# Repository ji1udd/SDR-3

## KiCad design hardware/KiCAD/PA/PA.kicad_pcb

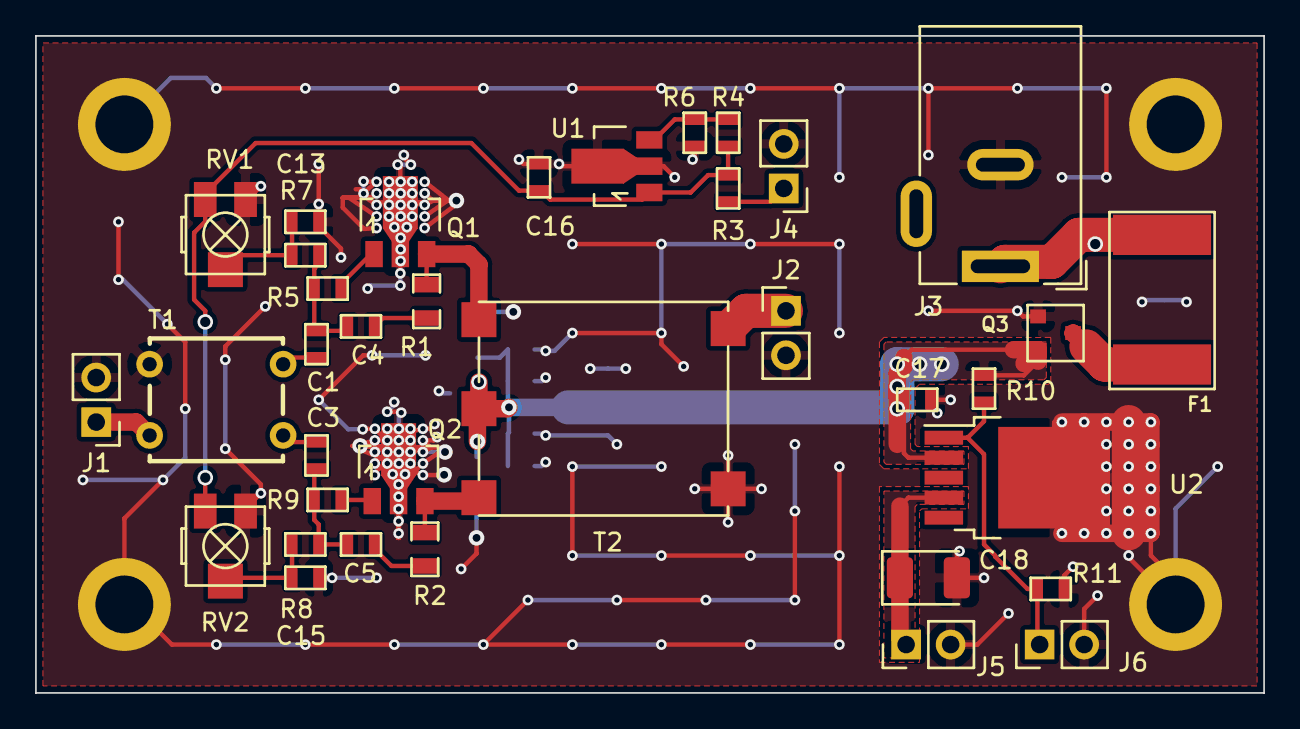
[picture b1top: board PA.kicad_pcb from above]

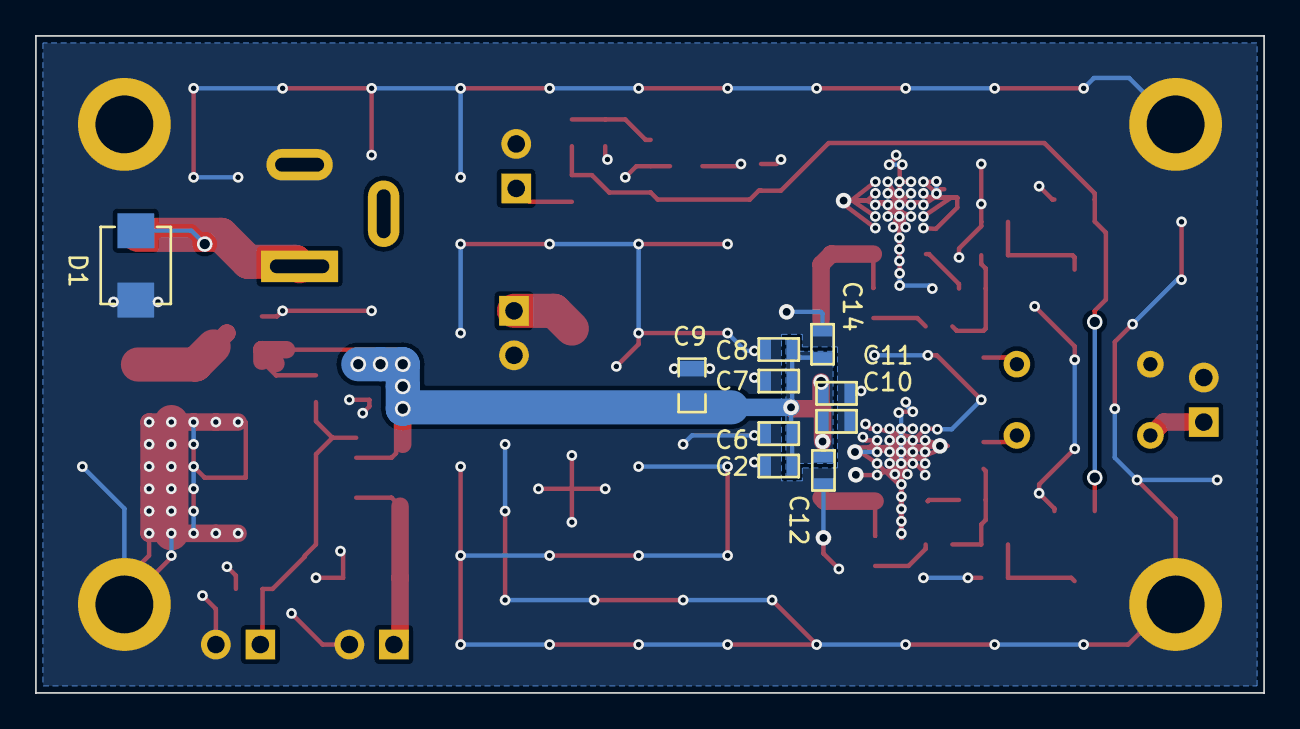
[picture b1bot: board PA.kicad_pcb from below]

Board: 2 copper layers, 70.1 x 37.5 mm, 50 parts (10 on the bottom side), 23 nets.

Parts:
C1, C3, C10, C11, C12, C13, C14, C15: 100n; SM0603
C2, C6, C7, C8, C16: 1u; SM0603
C4, C5: DNI; SM0603
C9: 47u; SM0805
C17: 0.33u; SM0603
C18: 22u; CP_EIA-3528-15_AVX-H_Pad1.50x2.35mm_HandSolder
D1: SMBJ18CA; smbj18ca
F1: Polyfuse; FUSE
J1, J2, J4, J5, J6: Conn_01x02; PinHeader_1x02_P2.54mm_Vertical
J3: Barrel_Jack; BarrelJack_Wuerth_6941xx301002
MH1, MH2, MH3, MH4: TestPoint; m3
Q1, Q2: RFM04U6P; SOT89-3_Housing_RevA_02Sep2012
Q3: DMP3099L; SOT23_3
R1, R2: DNI; SM0805
R3: 2700; SM0603
R4: 470; SM0603
R5, R9: 4.7; SM0603
R6: 1500; SM0603
R7, R8: 100; SM0603
R10: 10k; SM0603
R11: DNI; SM0603
RV1, RV2: 1000; TS4YJ
T1: BN43-2402; BN43-2402_TRNS
T2: B62152A4X30; B62152A4X30_TRNS
U1: TA76431F; SOT89-3_Housing_RevA_02Sep2012
U2: BA50BC0WFP; TO-252-5_TabPin6

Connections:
/7.2V: C2.2, C6.2, C7.2, C8.2, C9.1, C10.2, C11.2, C12.2, C14.2, C17.2, Q3.2, R10.2, T2.2, U2.2
/VG1: C13.1, R7.1, RV1.2
/VG2: C15.1, R8.1, RV2.2
GND: C2.1, C6.1, C7.1, C8.1, C9.2, C10.1, C11.1, C12.1, C13.2, C14.1, C15.2, C16.2, C17.1, C18.2, D1.2, J1.2, J2.2, J3.2, J4.2, J5.2, J6.2, MH1.1, MH2.1, MH3.1, MH4.1, Q1.2, Q2.2, Q3.1, R6.1, R11.1, RV1.3, RV2.3, T1.2, T2.5, U1.2, U2.6
unnamed: C1.1, T1.4
unnamed: C1.2, C4.1, R5.1, R7.2
unnamed: C3.1, T1.3
unnamed: C3.2, C5.1, R8.2, R9.1
unnamed: C4.2, R1.1
unnamed: C5.2, R2.1
unnamed: C16.1, R3.2, R4.2, RV1.1, RV2.1, U1.1
unnamed: C18.1, J5.1, U2.4
unnamed: D1.1, F1.2, J3.1
unnamed: F1.1, Q3.3
unnamed: J1.1, T1.1
unnamed: J2.1, T2.4
unnamed: J4.1, R3.1
unnamed: J6.1, R10.1, R11.2, U2.1
unnamed: Q1.1, R5.2
unnamed: Q1.3, R1.2, T2.1
unnamed: Q2.1, R9.2
unnamed: Q2.3, R2.2, T2.3
unnamed: R4.1, R6.2, U1.3

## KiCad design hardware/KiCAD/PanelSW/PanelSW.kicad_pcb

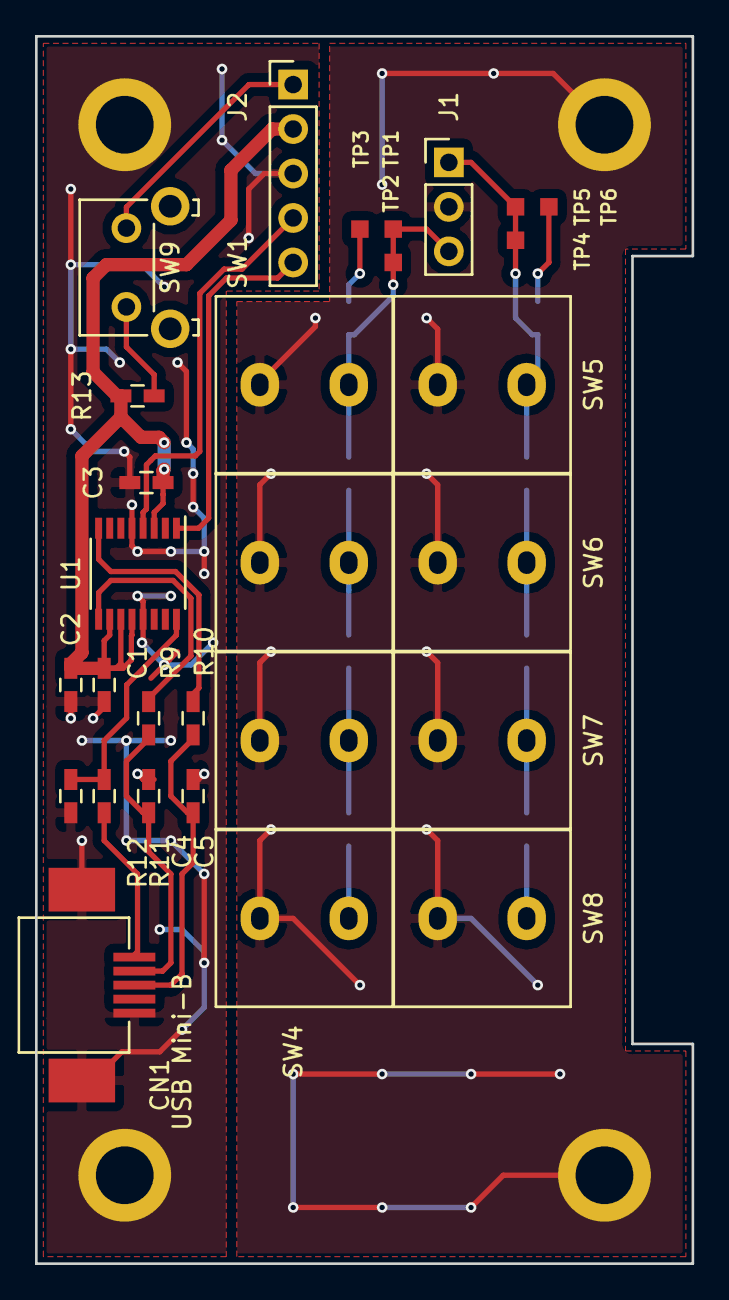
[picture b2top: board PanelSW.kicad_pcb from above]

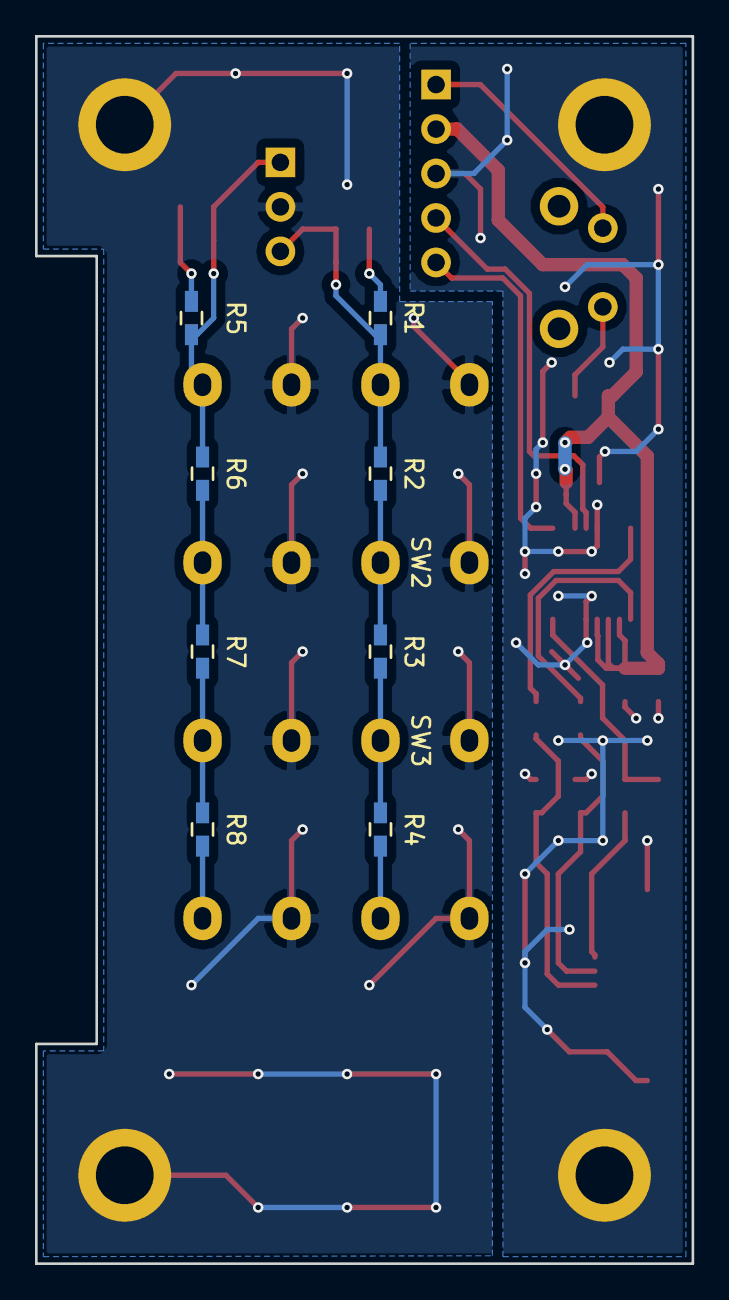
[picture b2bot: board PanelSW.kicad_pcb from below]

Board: 2 copper layers, 37.5 x 70.1 mm, 41 parts (8 on the bottom side), 23 nets.

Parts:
C1, C3: 100n; C_0603_HandSoldering
C2: 4.7u; C_0603_HandSoldering
C4, C5: 47p; C_0603_HandSoldering
CN1: USB Mini-B; UX60SC-MB-5ST
J1: Conn_01x03; PinHeader_1x03_P2.54mm_Vertical
J2: Conn_01x05; PinHeader_1x05_P2.54mm_Vertical
MH1, MH2, MH3, MH4: TestPoint; m3
R1, R5: 220; C_0603_HandSoldering
R2, R6: 270; C_0603_HandSoldering
R3, R7: 330; C_0603_HandSoldering
R4, R8: 470; C_0603_HandSoldering
R9, R10: 27; C_0603_HandSoldering
R11: 4.7k; C_0603_HandSoldering
R12: 10k; C_0603_HandSoldering
R13: 1k; C_0603_HandSoldering
SW1, SW2, SW3, SW4, SW5, SW6, SW7, SW8: SW_Push; SW_CW_DS660RS
SW9: SW_Push; SW_Tactile_SKHH_Angled
TP1, TP2, TP3, TP4, TP5, TP6: TestPoint; TP
U1: FT230XS; SSOP-16_3.9x4.9mm_P0.635mm

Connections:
GND: C1.2, C2.2, C3.2, C4.1, C5.2, CN1.5, CN1.6, CN1.7, J2.3, MH1.1, MH4.1, R12.1, U1.5, U1.13
GNDA: J1.2, MH2.1, MH3.1, SW1.1, SW2.1, SW3.1, SW4.1, SW5.1, SW6.1, SW7.1, SW8.1
unnamed: C1.1, C2.1, C3.1, J2.2, R13.1, U1.3, U1.10, U1.11, U1.12
unnamed: C4.2, CN1.2, R9.2
unnamed: C5.1, CN1.3, R10.2
unnamed: CN1.1, R11.2
unnamed: J1.1, R5.1, R6.2, SW5.2, TP4.1, TP5.1
unnamed: J1.3, R1.1, R2.2, SW1.2, TP1.1, TP2.1
unnamed: J2.1, SW9.2
unnamed: J2.4, U1.4
unnamed: J2.5, U1.1
unnamed: R1.2, TP3.1
unnamed: R2.1, R3.2, SW2.2
unnamed: R3.1, R4.2, SW3.2
unnamed: R4.1, SW4.2
unnamed: R5.2, TP6.1
unnamed: R6.1, R7.2, SW6.2
unnamed: R7.1, R8.2, SW7.2
unnamed: R8.1, SW8.2
unnamed: R9.1, U1.9
unnamed: R10.1, U1.8
unnamed: R11.1, R12.2, U1.16
unnamed: R13.2, SW9.1

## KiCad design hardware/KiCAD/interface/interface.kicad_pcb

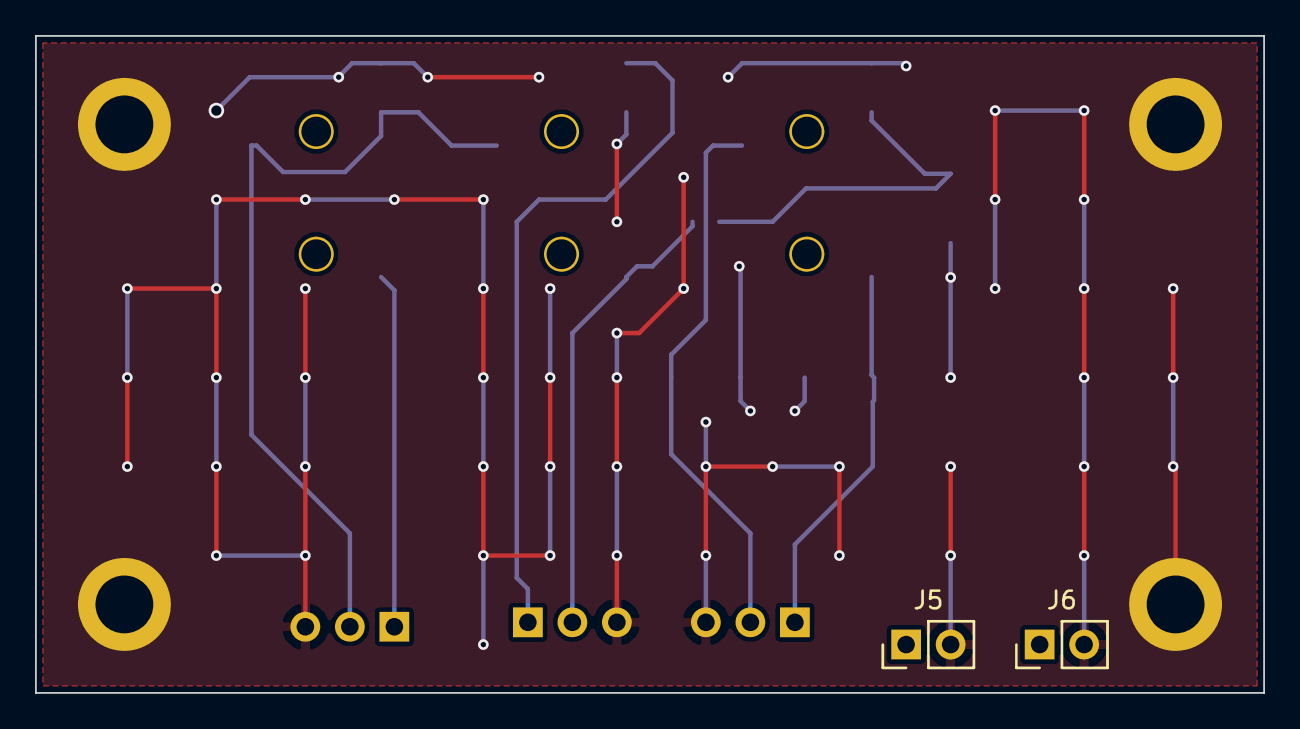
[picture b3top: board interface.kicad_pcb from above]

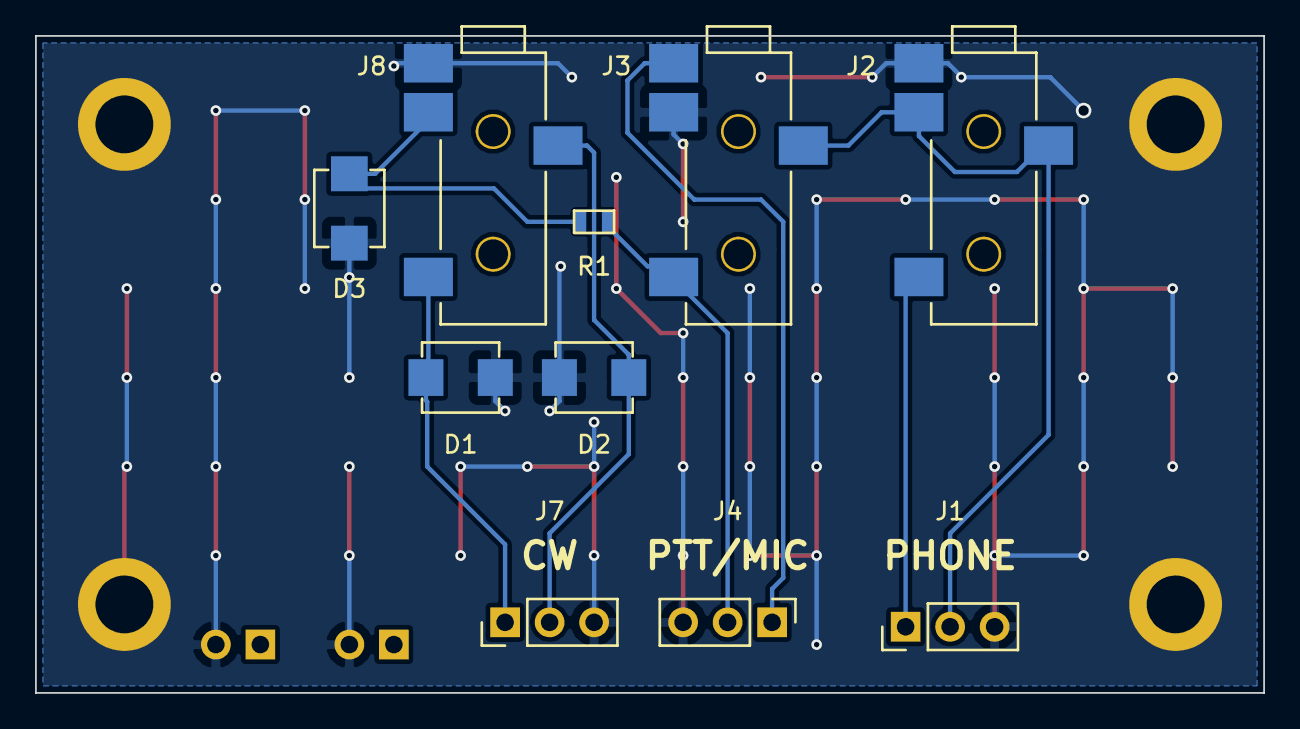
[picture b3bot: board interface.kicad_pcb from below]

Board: 2 copper layers, 70.1 x 37.5 mm, 16 parts (10 on the bottom side), 8 nets.

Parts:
D1, D2, D3: SMBJ18CA; smbj18ca
J1, J4, J7: Conn_01x03; PinHeader_1x03_P2.54mm_Vertical
J2, J3, J8: SJ-43514-SMT
J5, J6: Conn_01x02; PinHeader_1x02_P2.54mm_Vertical
MH1, MH2, MH3, MH4: TestPoint; m3
R1: DNI; SM0603

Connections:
GND: D1.2, D2.2, D3.2, J1.3, J2.1, J3.4, J4.3, J5.2, J6.2, J7.3, J8.1, MH1.1, MH2.1, MH3.1, MH4.1
unnamed: D1.1, J7.1, J8.2
unnamed: D2.1, J7.2, J8.3
unnamed: D3.1, J8.4, R1.1
unnamed: J1.1, J2.2
unnamed: J1.2, J2.3, J2.4, J3.3
unnamed: J3.1, J4.1
unnamed: J3.2, J4.2, R1.2

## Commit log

2018-10-06 1st Summary (Step1 to 4)
2018-10-08 Added Step5 modification
2018-10-12 Added keyer setting menu
2018-10-14 added bug key / straight key function as Step7
2018-10-14 bug fix
2018-10-14 added keyer speed setting on tranceiver as Step8
2018-10-20 added Step9 and Step10
2018-10-22 added 4 type Rx LPF ( fc = 600,700,800,900Hz )
2018-10-24 added CW Rx filter (8th order IIR HPF/LPF) as Step11
2018-10-28 changed CW rise time as Step12
2018-11-13 T2 Mixer LTSpice model
2018-11-16 added T2 Mixer comparison spice model
2018-11-18 Added an analog type S-meter as Step13
2018-11-18 fixed README.md
2018-11-18 Fixed README.md again
2018-11-21 Updated Step13_gui_c_2.txt
2018-11-21 Updated Step13_gui_c_2.jpg (bug fix)
2018-11-25 Update S-meter as Step14. a bitmap data of S-meter panel can be used.
2018-12-01 added Yado-san's designed s-meter and setting as Step15
2018-12-01 added No.2 tips on README.md
2018-12-08 added Makino-san's and Gyofun-san's designed s-meters as Step16
2018-12-19 fixed bugs in Step13 as Step17
2018-12-22 added Tx Meter function as Step18
2018-12-22 fixed type1 and type3 meter on tx
2018-12-27 add Battery voltage monitor (Yado-san's idea) as Step19
2019-01-13 Added Rig communication function as Step20
2019-01-13 no message
2019-01-19 Waterfall is added as Step21
2019-02-05 added Squelch function (Gyofun-san's idea) as Step22
2019-02-12 Fix 10ms dispatch as Step23
2019-02-13 fix squelch bug as Step24
2019-02-17 added Memory Keyer function
2019-02-19 fixed Tx fs48kHz LPF bug
2019-02-24 Updated Memory Keyer function as Step27
2019-02-24 Updated README.md, Step27 is under debugging.
2019-03-02 Fixed Step27 bugs
2019-03-04 Fixed Step27 bug again (additional patch part2)
2019-03-30 release schematic, bom, gerber and photos
2019-04-13 fixed Tx mute bug as Step28
2019-04-20 updated rigctrl function as Step29
2019-04-30 added External PTT as Step30
2019-06-28 Uploaded Hilbert filter option as Option1
2019-07-07 JA3GSE designed 511taps Hilbert filter as Option2
2019-09-01 Added Choshoshinsya-san's idea as option3
2019-09-01 Uploaded Option3 files
2020-06-14 Added DDC/DUC board
2020-06-20 Added DDC-DUC board schematic and BOM
2020-07-05 fixed
2020-07-24 added ddc-duc stm32f405 firmware
2020-07-24 Added ddc-duc MAX10 gateware
2020-07-24 Added ddc-duc tranceiver schematic
2020-10-17 Improved DDC-DUC firmware (tuning dia l Acceleration)
2021-06-06 SO2R TRX
